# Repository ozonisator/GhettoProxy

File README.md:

# GhettoProxy
Ghetto Proxy Huckepackplatine für den SI4432 OpenLRSng Empfänger

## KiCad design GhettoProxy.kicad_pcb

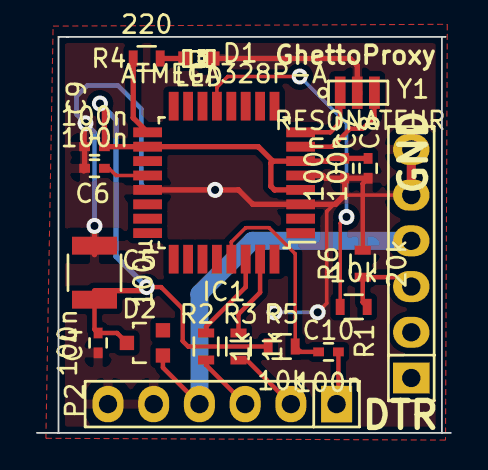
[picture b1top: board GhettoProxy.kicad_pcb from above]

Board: 2 copper layers, 23.0 x 22.0 mm, 19 parts (0 on the bottom side), 16 nets.

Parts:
C4, C6, C7, C8, C9, C10: 100n; C_0402
C5: 100µ; C_1210
D1: LED; LED-0603
D2: BAT54s; Diode_SOT23
IC1: ATMEGA328P-A; TQFP-32_7x7mm_Pitch0.8mm
P1: OpenLRS; Pin_Header_Straight_1x06
P2: Telemetrie; Pin_Header_Straight_1x06
R1, R5: 10k; R_0603
R2, R3: 1k; R_0603
R4: 220; R_0603
R6: 20k; R_0603
Y1: RESONATEUR; CerOsc_3,2x1,3

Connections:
+5V: C4.1, C5.1, C7.1, C8.1, C9.1, D2.2, IC1.4, IC1.6, IC1.18, R5.1
/DTR: C10.2, P2.1
/LTMOUT: P1.3, R1.1, R6.1
/RX: P2.3, R2.1
/TX: P2.2, R3.1
GND: C4.2, C5.2, C6.2, C7.2, C8.2, C9.2, D1.2, IC1.3, IC1.5, IC1.21, P1.5, P1.6, P2.5, P2.6, R6.2, Y1.2
unnamed: C6.1, IC1.20
unnamed: C10.1, IC1.29, R5.2
unnamed: D1.1, R4.1
unnamed: D2.1, P1.4, P2.4
unnamed: IC1.7, Y1.3
unnamed: IC1.8, Y1.1
unnamed: IC1.13, R1.2
unnamed: IC1.17, R4.2
unnamed: IC1.30, R2.2
unnamed: IC1.31, R3.2

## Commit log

2015-02-05 Bestückungsdruck aufgeräumt
2015-02-06 3,3V LDO entfernt (macht keinen Sinn und kostet nur Geld), Platine verkleinert
